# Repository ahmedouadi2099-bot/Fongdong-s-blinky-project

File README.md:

# Fongdong-s-blinky-project
A led chaser guided project

Hardware :

1)NE555P Timer

2)4017 IC

3)2 Resistors(1k ohm and 470 ohm)

4)1 Potentiometer

5)1 Normal Capacitor

6)1 Polarized Capacitor

7)10 LEDs

3d OverView:

Schematics:

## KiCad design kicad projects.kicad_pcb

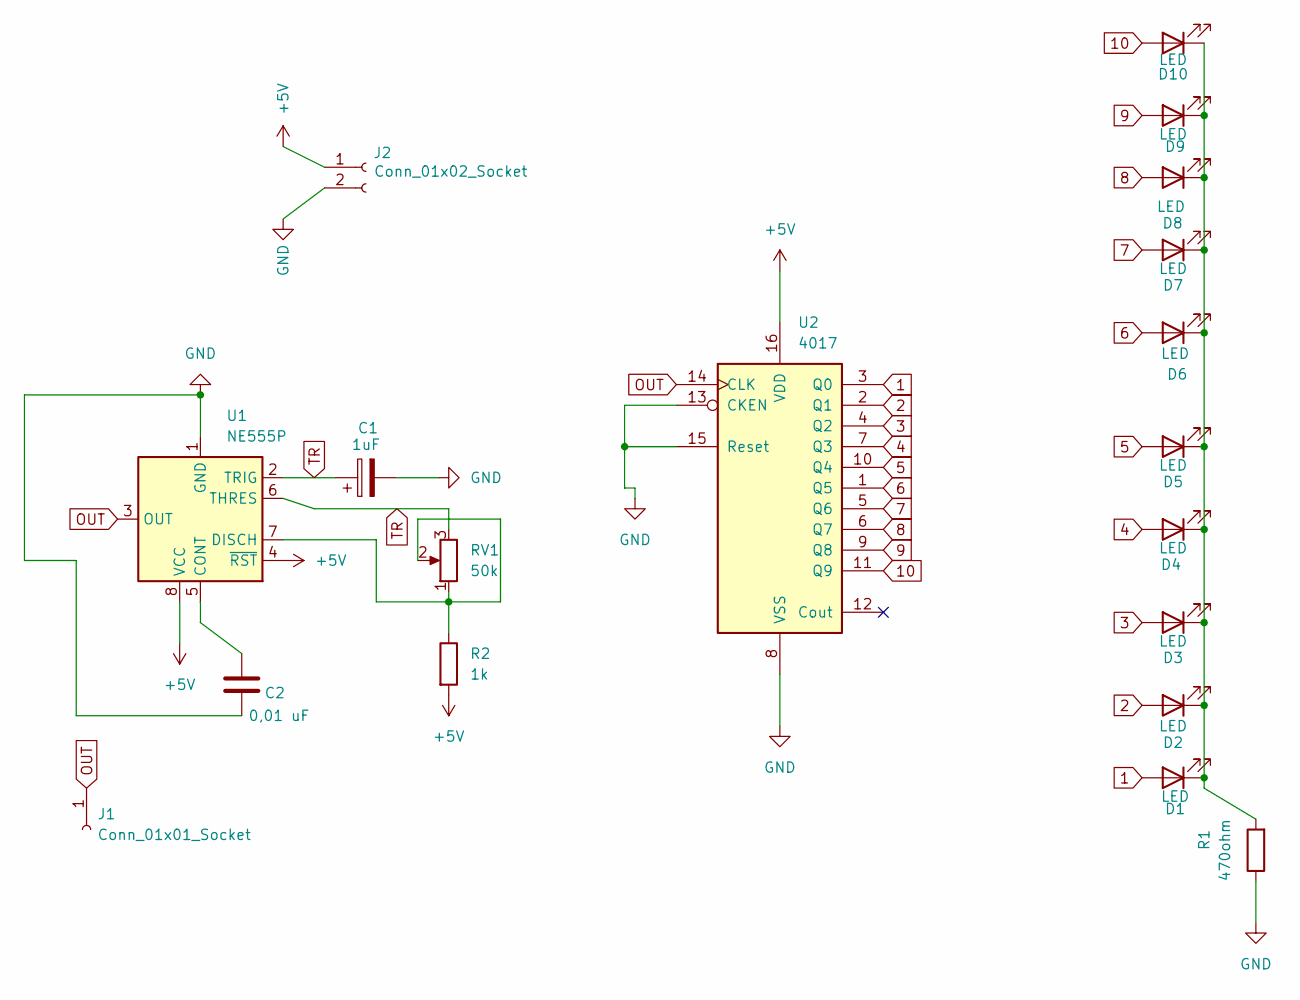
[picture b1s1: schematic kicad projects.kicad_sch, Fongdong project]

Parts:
C1: 1uF; CP_Radial_D5.0mm_P2.00mm
C2: 0,01 uF; C_Disc_D7.5mm_W2.5mm_P5.00mm
D1, D2, D3, D4, D5, D6, D7, D8, D9, D10: LED; LED_D3.0mm
J1: Conn_01x01_Socket; PinHeader_1x01_P2.54mm_Vertical
J2: Conn_01x02_Socket; PinHeader_1x02_P2.54mm_Vertical
R1: 470ohm; R_Axial_DIN0207_L6.3mm_D2.5mm_P7.62mm_Horizontal
R2: 1k; R_Axial_DIN0207_L6.3mm_D2.5mm_P7.62mm_Horizontal
RV1: 50k; Potentiometer_Vishay_T93YA_Vertical
U1: NE555P; DIP-8_W7.62mm
U2: 4017; DIP-16_W7.62mm

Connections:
1: D1.2 (A), U2.3 (Q0)
2: D2.2 (A), U2.2 (Q1)
3: D3.2 (A), U2.4 (Q2)
4: D4.2 (A), U2.7 (Q3)
5: D5.2 (A), U2.10 (Q4)
6: D6.2 (A), U2.1 (Q5)
7: D7.2 (A), U2.5 (Q6)
8: D8.2 (A), U2.6 (Q7)
9: D9.2 (A), U2.9 (Q8)
10: D10.2 (A), U2.11 (Q9)
+5V: J2.1, R2.2, U1.4 (~RST), U1.8 (VCC), U2.16 (VDD)
GND: C1.2, C2.2, J2.2, R1.1, U1.1 (GND), U2.8 (VSS), U2.13 (CKEN), U2.15 (Reset)
unnamed: D1.1 (K), D2.1 (K), D3.1 (K), D4.1 (K), D5.1 (K), D6.1 (K), D7.1 (K), D8.1 (K), D9.1 (K), D10.1 (K), R1.2
unnamed: C2.1, U1.5 (CONT)
unnamed: R2.1, RV1.1, RV1.2, U1.7 (DISCH)
OUT: J1.1, U1.3 (OUT), U2.14 (CLK)
TR: C1.1, RV1.3, U1.2 (TRIG), U1.6 (THRES)

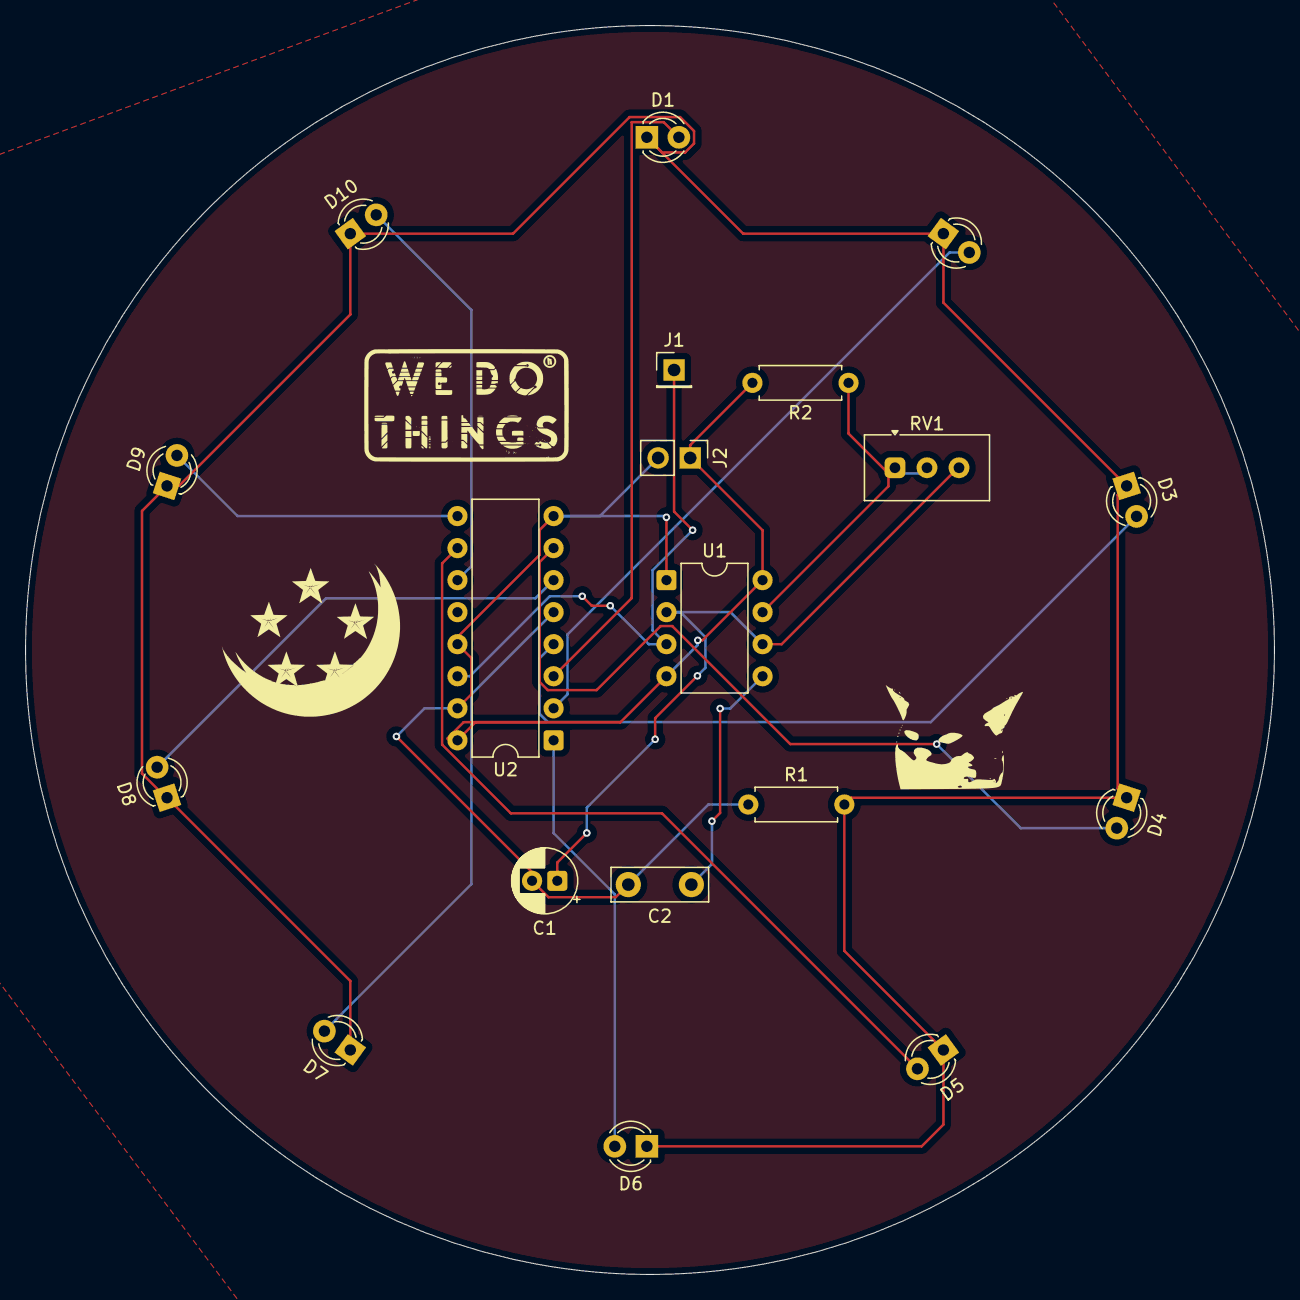
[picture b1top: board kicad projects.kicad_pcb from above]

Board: 2 copper layers, 99.0 x 99.0 mm, 19 parts (0 on the bottom side), 17 nets.
